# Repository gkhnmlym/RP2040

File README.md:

# RP2040

"RP2040 is a microcontroller chip developed by Raspberry Pi, based on the ARM Cortex-M0+ core. This chip has gained popularity due to several advantages, especially for embedded systems and microcontroller projects. Here are some of the advantages of RP2040:

-Performance: RP2040 features an ARM Cortex-M0+ core running at 133MHz, allowing it to execute complex operations quickly and deliver efficient performance in high-speed applications.

-Expandable Memory: RP2040 comes with 264 KB of internal SRAM, and it offers options for expandable memory using external devices like SPI Flash.

-Multiple I/O Options: With a large number of I/O pins, RP2040 can be used for various purposes, including digital and analog inputs/outputs, UART, I2C, SPI, and PWM. This enables easy integration with a wide range of sensors, displays, and other external devices.

-Low-Jitter Clock: RP2040 generates a low-jitter clock, which is beneficial for applications requiring precise timing. It ensures better performance in tasks involving audio, video, and other synchronization needs.

-Flexible Development Environment: Raspberry Pi provides the RP2040 SDK and Arduino Core, making it easy for developers to work on RP2040-based projects using various programming languages and tools.

-Low Power Consumption: RP2040 incorporates low-power modes and optimized operation modes, resulting in energy efficiency. This feature is advantageous for battery-powered applications, providing a longer battery life.

-Cost-Effective: RP2040 is a budget-friendly microcontroller chip, making it an ideal choice to reduce project costs and cater to a wide user base.

-Community Support: Being backed by a vast community, RP2040-based projects benefit from a platform where users can share knowledge, experiences, and receive assistance.

-All these advantages make RP2040 a popular choice for embedded systems, hobby electronics, and microcontroller-based projects."

The image below shows the PCB layout with KiCad design.

You can get help from the link for the software.

-( https://www.youtube.com/watch?v=i8MqFmR0W3E )

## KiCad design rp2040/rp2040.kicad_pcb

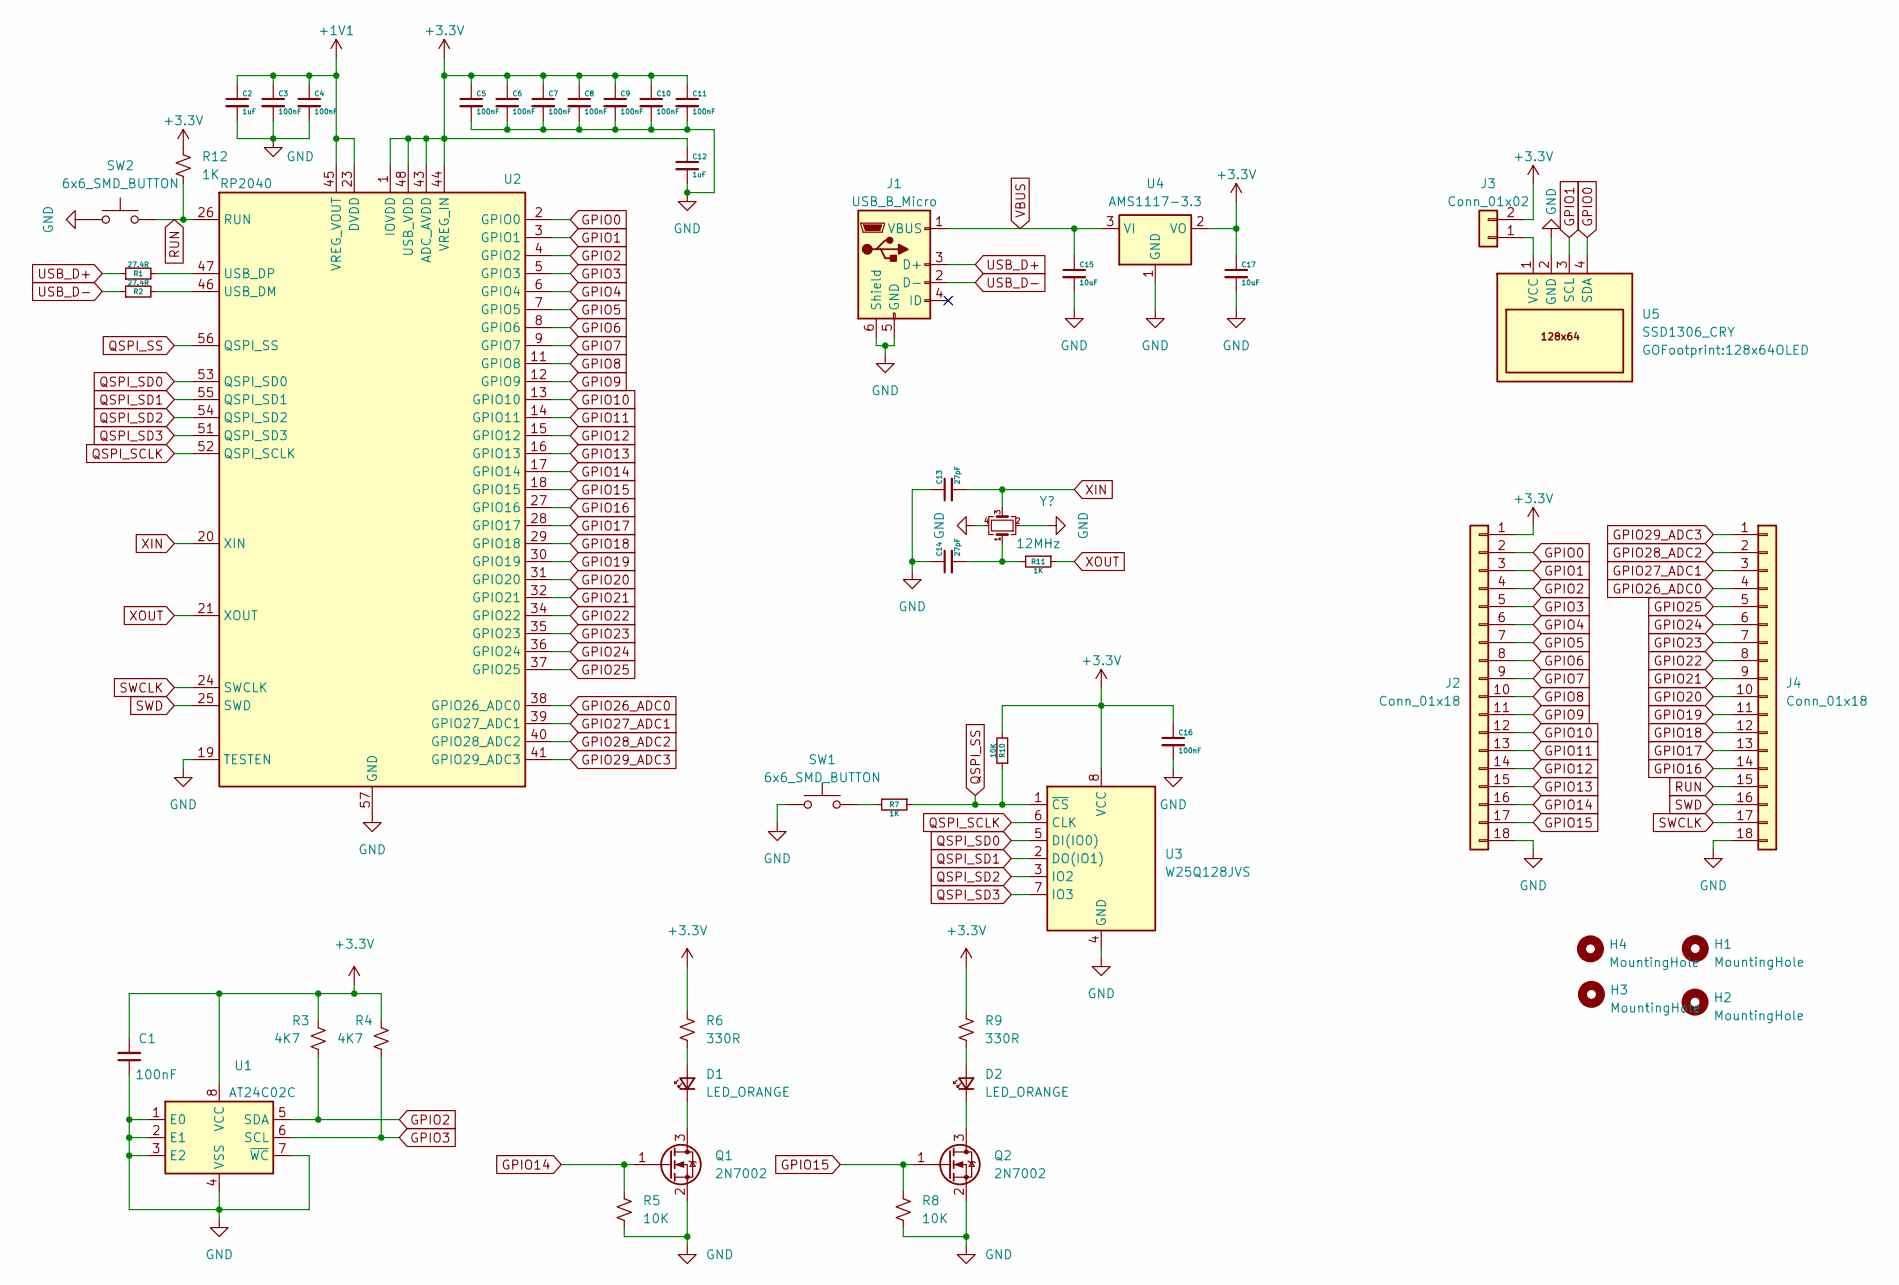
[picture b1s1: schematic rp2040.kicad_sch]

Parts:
C1: 100nF; C_0805_2012Metric
C2, C12: 1uF; C_0603_1608Metric
C3, C4, C5, C6, C7, C8, C9, C10, C11, C16: 100nF; C_0603_1608Metric
C13, C14: 27pF; C_0603_1608Metric
C15, C17: 10uF; C_0603_1608Metric
D1, D2: LED_ORANGE; LED_0805_2012Metric
H1, H2, H3, H4: MountingHole; MountingHole_3.2mm_M3_Pad_Via
J1: USB_B_Micro; USB_Micro-B_GCT_USB3076-30-A
J2, J4: Conn_01x18; PinHeader_1x18_P2.54mm_Vertical
J3: Conn_01x02; PinHeader_1x02_P2.54mm_Vertical
Q1, Q2: 2N7002; SOT-23
R1, R2: 27.4R; R_0603_1608Metric
R3, R4: 4K7; R_0805_2012Metric
R5, R8: 10K; R_0805_2012Metric
R6, R9: 330R; R_0805_2012Metric
R7, R11: 1K; R_0603_1608Metric
R10: 10K; R_0603_1608Metric
R12: 1K; R_0805_2012Metric
SW1, SW2: 6x6_SMD_BUTTON; SW_SPST_CK_RS282G05A3
U1: AT24C02C; SOIC-8_3.9x4.9mm_P1.27mm
U2: RP2040; QFN-56-1EP_7x7mm_P0.4mm_EP3.2x3.2mm
U3: W25Q128JVS; SOIC-8_5.23x5.23mm_P1.27mm
U4: AMS1117-3.3; SOT-223-3_TabPin2
U5: SSD1306_CRY; 128x64OLED
Y1: 12MHz; Crystal_SMD_5032-4Pin_5.0x3.2mm

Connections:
+1V1: C2.1, C3.1, C4.1, U2.23 (DVDD), U2.45 (VREG_VOUT), U2.50 (DVDD)
+3.3V: C1.2, C5.1, C6.1, C7.1, C8.1, C9.1, C10.1, C11.1, C12.1, C16.1, C17.1, J2.1, J3.2, R3.1, R4.1, R6.2, R9.2, R10.2, R12.2, U1.8 (VCC), U2.1 (IOVDD), U2.10 (IOVDD), U2.22 (IOVDD), U2.33 (IOVDD), U2.42 (IOVDD), U2.43 (ADC_AVDD), U2.44 (VREG_IN), U2.48 (USB_VDD), U2.49 (IOVDD), U3.8 (VCC), U4.2 (VO)
GND: C1.1, C2.2, C3.2, C4.2, C5.2, C6.2, C7.2, C8.2, C9.2, C10.2, C11.2, C12.2, C13.1, C14.1, C15.2, C16.2, C17.2, J1.5 (GND), J1.6 (Shield), J2.18, J4.18, Q1.2 (S), Q2.2 (S), R5.2, R8.2, SW1.1, SW2.1, U1.1 (E0), U1.2 (E1), U1.3 (E2), U1.4 (VSS), U1.7 (~WC), U2.19 (TESTEN), U2.57 (GND), U3.4 (GND), U4.1 (GND), U5.2 (GND), Y1.2, Y1.4
GPIO0: J2.2, U2.2 (GPIO0), U5.4 (SDA)
GPIO1: J2.3, U2.3 (GPIO1), U5.3 (SCL)
GPIO2: J2.4, R3.2, U1.5 (SDA), U2.4 (GPIO2)
GPIO3: J2.5, R4.2, U1.6 (SCL), U2.5 (GPIO3)
GPIO4: J2.6, U2.6 (GPIO4)
GPIO5: J2.7, U2.7 (GPIO5)
GPIO6: J2.8, U2.8 (GPIO6)
GPIO7: J2.9, U2.9 (GPIO7)
GPIO8: J2.10, U2.11 (GPIO8)
GPIO9: J2.11, U2.12 (GPIO9)
GPIO10: J2.12, U2.13 (GPIO10)
GPIO11: J2.13, U2.14 (GPIO11)
GPIO12: J2.14, U2.15 (GPIO12)
GPIO13: J2.15, U2.16 (GPIO13)
GPIO14: J2.16, Q1.1 (G), R5.1, U2.17 (GPIO14)
GPIO15: J2.17, Q2.1 (G), R8.1, U2.18 (GPIO15)
GPIO16: J4.14, U2.27 (GPIO16)
GPIO17: J4.13, U2.28 (GPIO17)
GPIO18: J4.12, U2.29 (GPIO18)
GPIO19: J4.11, U2.30 (GPIO19)
GPIO20: J4.10, U2.31 (GPIO20)
GPIO21: J4.9, U2.32 (GPIO21)
GPIO22: J4.8, U2.34 (GPIO22)
GPIO23: J4.7, U2.35 (GPIO23)
GPIO24: J4.6, U2.36 (GPIO24)
GPIO25: J4.5, U2.37 (GPIO25)
GPIO26_ADC0: J4.4, U2.38 (GPIO26_ADC0)
GPIO27_ADC1: J4.3, U2.39 (GPIO27_ADC1)
GPIO28_ADC2: J4.2, U2.40 (GPIO28_ADC2)
GPIO29_ADC3: J4.1, U2.41 (GPIO29_ADC3)
unnamed: C14.2, R11.2, Y1.1
unnamed: D1.2 (A), R6.1
unnamed: D1.1 (K), Q1.3 (D)
unnamed: D2.2 (A), R9.1
unnamed: D2.1 (K), Q2.3 (D)
unnamed: J3.1, U5.1 (VCC)
unnamed: R7.2, SW1.2
unnamed: R2.2, U2.46 (USB_DM)
unnamed: R1.2, U2.47 (USB_DP)
QSPI_SCLK: U2.52 (QSPI_SCLK), U3.6 (CLK)
QSPI_SD0: U2.53 (QSPI_SD0), U3.5 (DI(IO0))
QSPI_SD1: U2.55 (QSPI_SD1), U3.2 (DO(IO1))
QSPI_SD2: U2.54 (QSPI_SD2), U3.3 (IO2)
QSPI_SD3: U2.51 (QSPI_SD3), U3.7 (IO3)
QSPI_SS: R7.1, R10.1, U2.56 (QSPI_SS), U3.1 (~CS)
RUN: J4.15, R12.1, SW2.2, U2.26 (RUN)
SWCLK: J4.17, U2.24 (SWCLK)
SWD: J4.16, U2.25 (SWD)
USB_D+: J1.3 (D+), R1.1
USB_D-: J1.2 (D-), R2.1
VBUS: C15.1, J1.1 (VBUS), U4.3 (VI)
XIN: C13.2, U2.20 (XIN), Y1.3
XOUT: R11.1, U2.21 (XOUT)

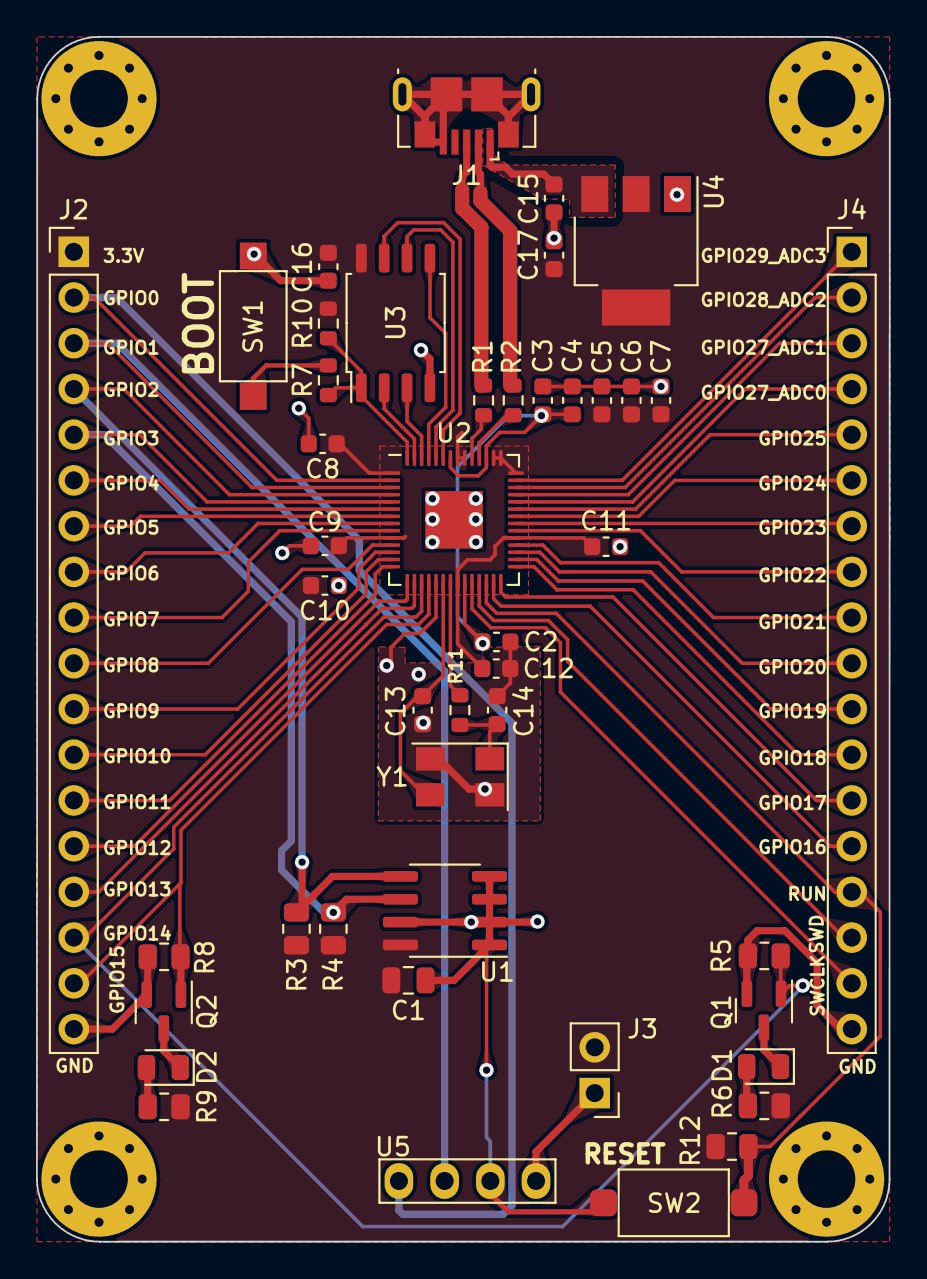
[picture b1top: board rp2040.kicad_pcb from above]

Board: 2 copper layers, 47.4 x 66.9 mm, 49 parts (0 on the bottom side), 56 nets.

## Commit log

2023-04-27 Upload
2023-04-27 datasheet
2023-06-22 edit pcb
2023-06-22 silkscreen fixed
2023-06-23 GERBER
2023-12-13 add Reset buton
2023-12-13 add teardrop
